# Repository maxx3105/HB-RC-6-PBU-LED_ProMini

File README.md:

# HB-RC-6-PBU-LED_ProMini
6-Fach Wandtaster mit Signal-Led auf Basis der AskSin++ für Homematic

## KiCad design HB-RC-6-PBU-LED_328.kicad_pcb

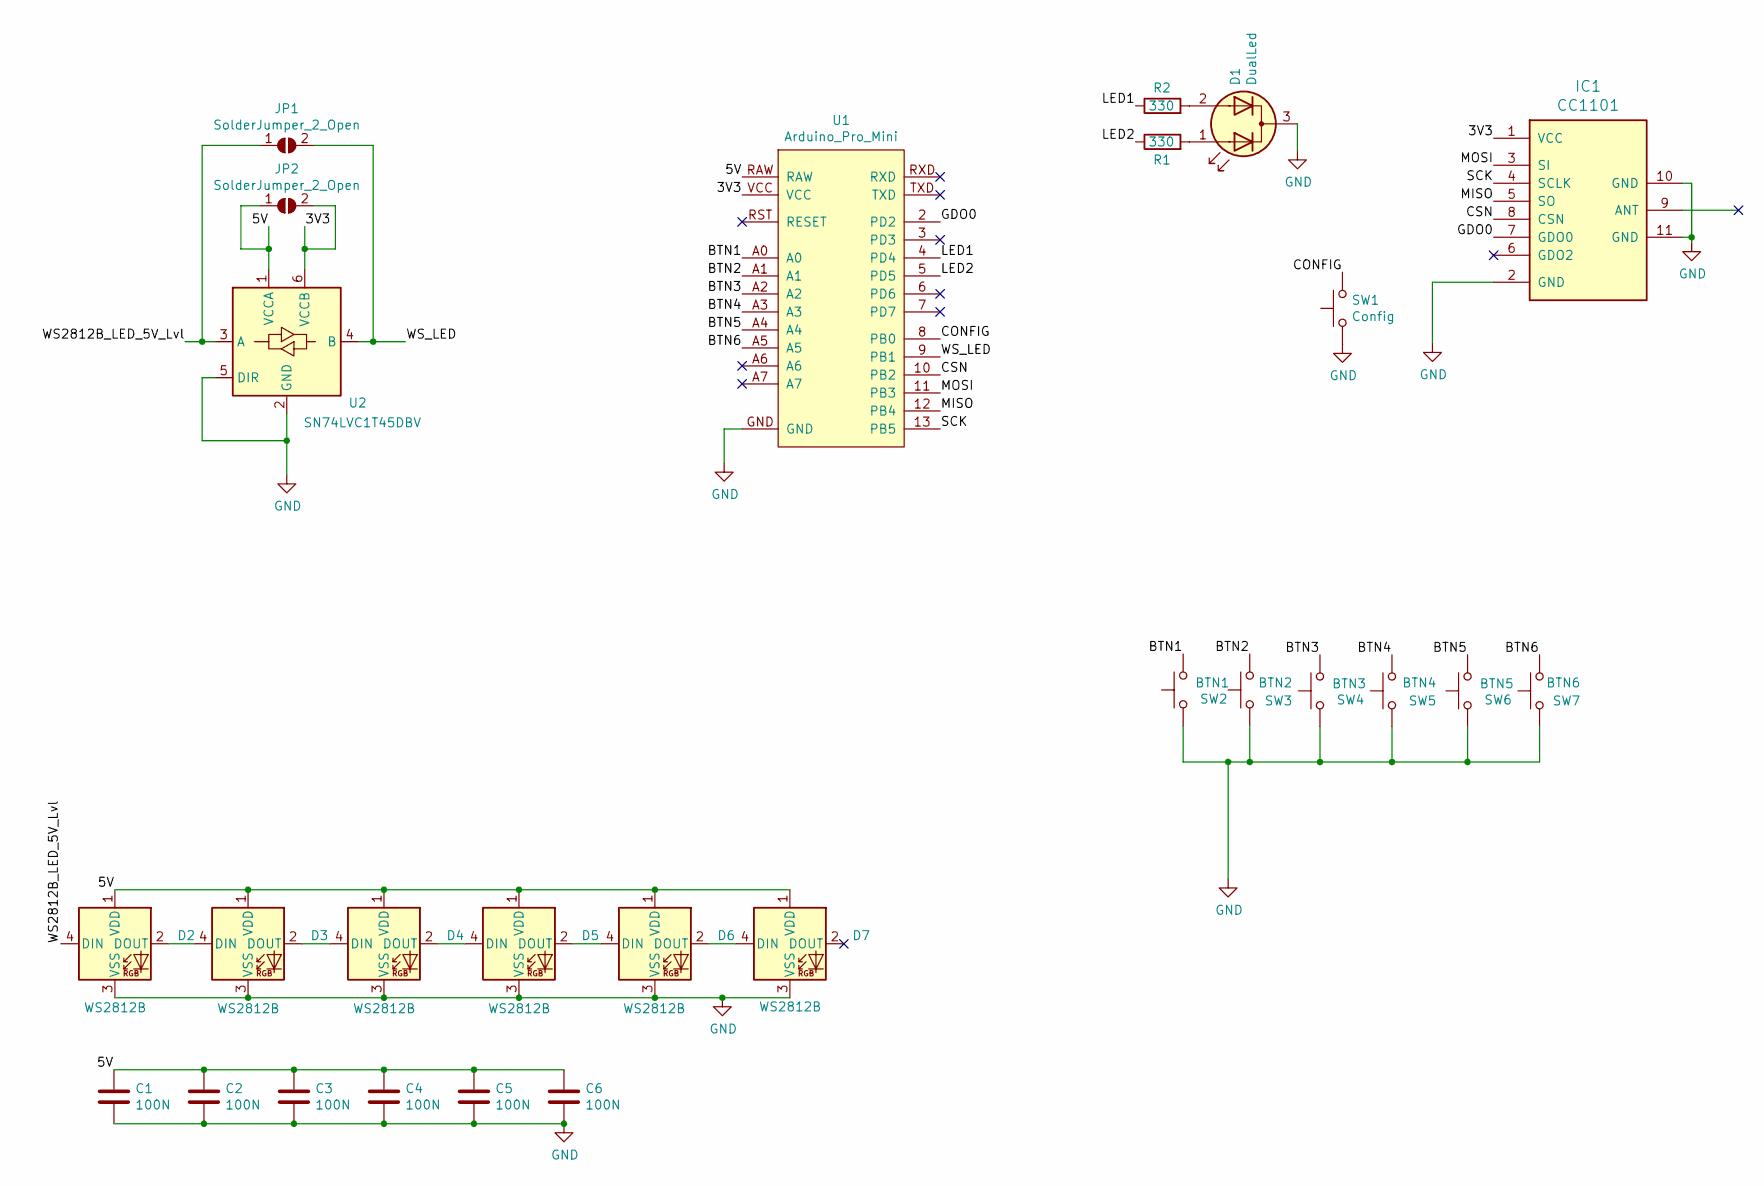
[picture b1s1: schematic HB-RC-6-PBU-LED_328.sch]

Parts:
C1, C2, C3, C4, C5, C6: 100N; C_0805_2012Metric_Pad1.18x1.45mm_HandSolder
D1: DualLed; LED_D3.0mm-3
D2, D3, D4, D5, D6, D7: WS2812B; LED_SK6812MINI_PLCC4_3.5x3.5mm_P1.75mm
IC1: CC1101; CC1101_SMD_THT_Ohne_Ant
JP1, JP2: SolderJumper_2_Open; SolderJumper-2_P1.3mm_Open_RoundedPad1.0x1.5mm
R1, R2: 330; R_0805_2012Metric_Pad1.20x1.40mm_HandSolder
SW1: Config; SW_SPST_FSMSM
SW2: BTN1; SW_SPST_FSMSM
SW3: BTN2; SW_SPST_FSMSM
SW4: BTN3; SW_SPST_FSMSM
SW5: BTN4; SW_SPST_FSMSM
SW6: BTN5; SW_SPST_FSMSM
SW7: BTN6; SW_SPST_FSMSM
U1: Arduino_Pro_Mini
U2: SN74LVC1T45DBV; SOT-23-6

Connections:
/3V3: IC1.1 (VCC), JP2.2 (B), U1.VCC, U2.6 (VCCB)
/5V: C1.1, C2.1, C3.1, C4.1, C5.1, C6.1, D2.1 (VDD), D3.1 (VDD), D4.1 (VDD), D5.1 (VDD), D6.1 (VDD), D7.1 (VDD), JP2.1 (A), U1.RAW, U2.1 (VCCA)
/BTN1: SW2.2, U1.A0
/BTN2: SW3.2, U1.A1
/BTN3: SW4.2, U1.A2
/BTN4: SW5.2, U1.A3
/BTN5: SW6.2, U1.A4
/BTN6: SW7.2, U1.A5
/CONFIG: SW1.2, U1.8 (PB0)
/CSN: IC1.8 (CSN), U1.10 (PB2)
/GDO0: IC1.7 (GDO0), U1.2 (PD2)
/LED1: R2.1, U1.4 (PD4)
/LED2: R1.1, U1.5 (PD5)
/MISO: IC1.5 (SO), U1.12 (PB4)
/MOSI: IC1.3 (SI), U1.11 (PB3)
/SCK: IC1.4 (SCLK), U1.13 (PB5)
/WS2812B_LED_5V_Lvl: D2.4 (DIN), JP1.1 (A), U2.3 (A)
/WS_LED: JP1.2 (B), U1.9 (PB1), U2.4 (B)
GND: C1.2, C2.2, C3.2, C4.2, C5.2, C6.2, D1.3 (K), D2.3 (VSS), D3.3 (VSS), D4.3 (VSS), D5.3 (VSS), D6.3 (VSS), D7.3 (VSS), IC1.2 (GND), IC1.10 (GND), IC1.11 (GND), SW1.1, SW2.1, SW3.1, SW4.1, SW5.1, SW6.1, SW7.1, U1.GND, U2.2 (GND), U2.5 (DIR)
unnamed: D1.1 (A1), R1.2
unnamed: D1.2 (A2), R2.2
unnamed: D2.2 (DOUT), D3.4 (DIN)
unnamed: D3.2 (DOUT), D4.4 (DIN)
unnamed: D4.2 (DOUT), D5.4 (DIN)
unnamed: D5.2 (DOUT), D6.4 (DIN)
unnamed: D6.2 (DOUT), D7.4 (DIN)

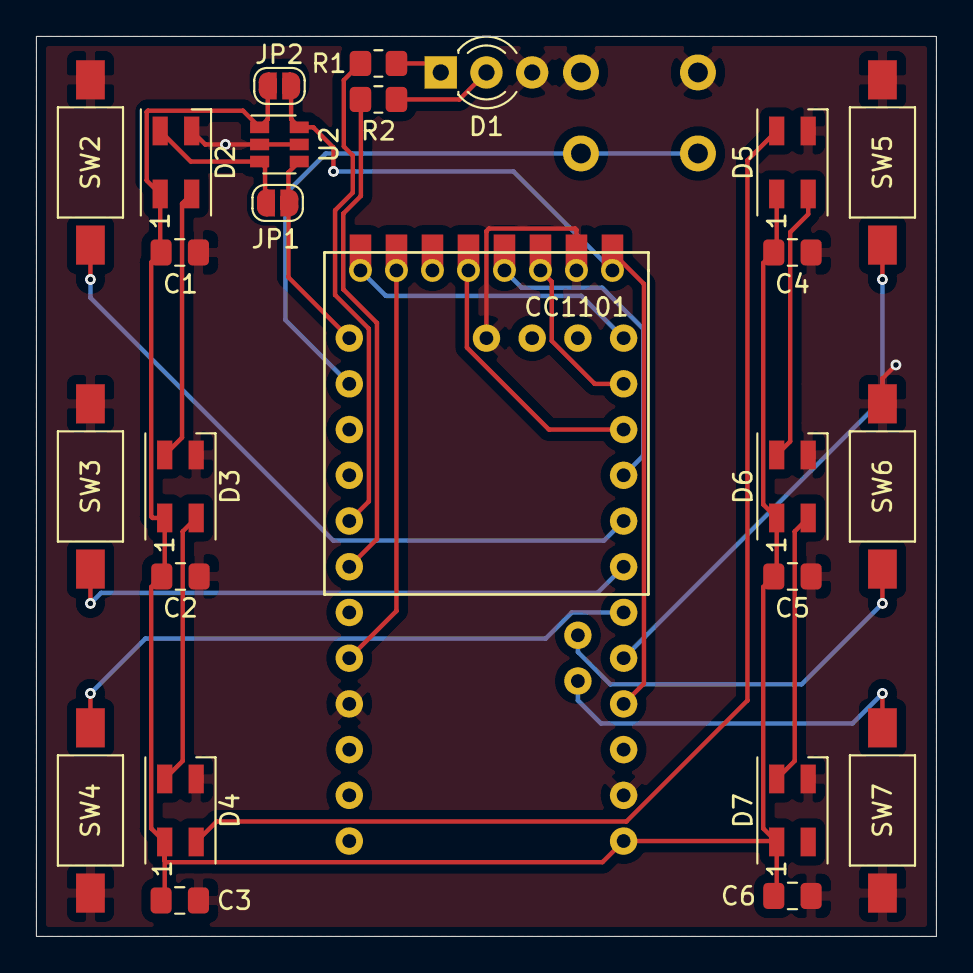
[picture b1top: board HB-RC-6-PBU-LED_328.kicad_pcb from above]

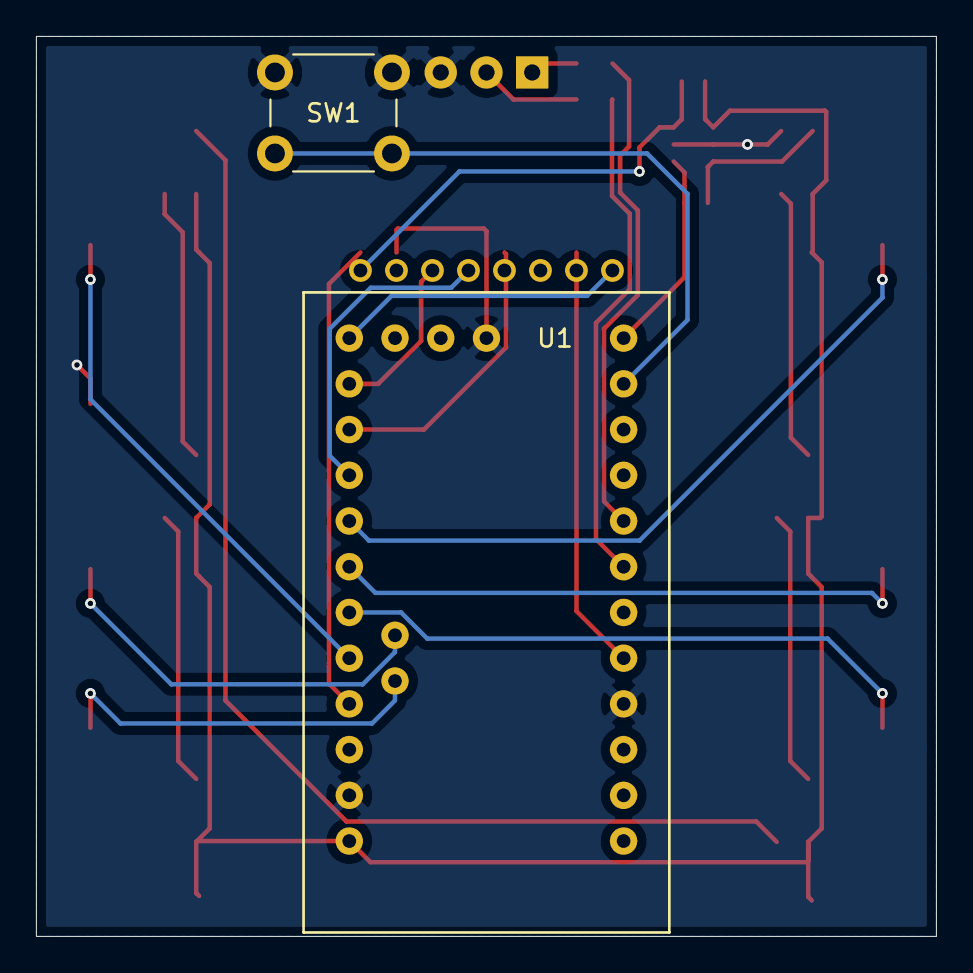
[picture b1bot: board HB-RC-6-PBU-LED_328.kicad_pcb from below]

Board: 2 copper layers, 50.0 x 50.0 mm, 27 parts (2 on the bottom side), 26 nets.
